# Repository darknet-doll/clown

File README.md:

# clown

A bubble-shooting clown costume. Make a gun shape with either hand, squeeze your
remaining fingers into your palm, and a comet of light runs from your upper arm
down to your fingertips — arriving exactly as a stream of bubbles starts firing out of
your fingers.

Two arms, two identical rigs — **one trigger per hand, each firing its own arm.**
LED strips hidden under gloves and sleeves, so the light reads as a glow coming
from inside the costume rather than a strip taped to your arm.

Each arm comes apart into four modules that unplug from each other, so you can get
out of the costume alone without turning into a pretzel.

**Start here:** [Clown-Build-Manual.pdf](Clown-Build-Manual.pdf) — the printable
manual. Page 1 is every part, numbered, with a plain-English note under each one;
every page after that is assembly steps referring back to those numbers.

Markdown equivalents, if you'd rather read them here:
[PARTS.md](PARTS.md) (parts and what they do) and
[BUILD.md](BUILD.md) (step-by-step assembly).

**Circuit:** [SCHEMATIC.md](SCHEMATIC.md) — two generated sheets, one for the
electronics and one for the harness. That's the drawing to review, and the one to
check your wiring against.

**Costume direction:** [DESIGN.md](DESIGN.md) — the concept board, and the three
places where it changes the build.

---

## Sequence

1. **Squeeze.** Microswitch in the palm closes.
2. **Motor kicks.** Blower gets a brief over-drive pulse to break static friction,
   then settles to its run speed.
3. **Comet launches** from pixel 0 at the pod, high on the upper arm, and travels
   toward the fingertips.
4. **~250 ms later** the comet lands at the fingertips and the blower has reached
   full speed — bubbles start. The light travel *is* the spin-up delay, so it
   reads as causal instead of as lag.
5. **Hold** to keep streaming; comets keep launching on a loop. The blower
   pulses at 5 Hz (100 ms on, 100 ms off, each burst kickstarted) rather than
   running steady — the bursts of speed form the bubbles better.
6. **Release.** Motor cuts, fingertips flare white and fade out.

---

## Why two independent arms

Each arm is a self-contained module: its own controller, battery, strip, blower,
and trigger. Nothing crosses the torso.

- No wire harness over the shoulders or back — nothing to snag, nothing to
  unplug when you take the costume off one sleeve at a time.
- **Each hand has its own trigger**, wired only to its own arm. There is no
  cross-arm wiring anywhere in v1.
- If one arm dies mid-event, the other keeps working.
- **The firmware is byte-identical on both.** As long as pixel 0 is at the pod
  on each arm, there's no handedness in the code — flash the same binary twice.

The tradeoff is buying two of everything, including two bubble maker kits and two
triggers. That's unavoidable regardless: you need one blower per hand.

*Later option:* the XIAO ESP32-C3 has ESP-NOW, so either trigger could **also** fire
the other arm for a two-handed blast. That's **additive** — each hand keeps its own
trigger and its own arm. It is a second way to fire, not a replacement for the
second trigger. Not in v1 — get one arm working end to end first.

---

## Modules and connectors

Nothing is soldered end to end across a joint. Each arm is four modules:

| Module | Holds | Unplugs at |
|---|---|---|
| **Pod** — upper arm | brain, boost, level shifter, MOSFET, fuse, disconnect, cell cradle, upper-arm strip 6 px | `SW1` + battery plug + straps |
| **Sleeve** — forearm | forearm strip, 15 px | elbow: SM 4-pin + SM 3-pin |
| **Glove** — hand | hand strip 6 px, this hand's trigger | wrist: SM 3-pin + SM 4-pin |
| **Bubbler** | bottle, cap, hose, blower head | hand: SM 2-pin + its strap |

### The connectors

| Boundary | Carries | Connector |
|---|---|---|
| Cell ↔ pod, cell ↔ charger | 2 | **JST-PH 2.0, 2-pin** *(factory, on the cell)* |
| Pod → upper-arm strip | strip 3 | **JST-SM 3-pin** |
| Strip across the elbow | strip 3 | **JST-SM 3-pin** |
| Pod → sleeve, at the elbow | motor 2 + trigger 2 | **JST-SM 4-pin** |
| Strip across the wrist | strip 3 | **JST-SM 3-pin** |
| Sleeve → glove, at the wrist | motor 2 + trigger 2 | **JST-SM 4-pin** |
| Motor ↔ bubbler, at the hand | motor 2 | **JST-SM 2-pin** |
| Microswitch pigtail | switch 2 | **JST-ZH 1.5 mm, 2-pin** |

The trigger and the motor both have to reach the pod from the hand, so they cross
*both* joints on one shared 4-pin lead — identical pinout at the elbow and the
wrist, the sleeve passes it straight through — while the strip crosses each joint
on its own 3-pin.

### Two rules that keep it safe

**No two connectors on one arm share both family and pin count** — with two
deliberate exceptions, both safe by construction. PH-2 · ZH-2 · SM-2 · SM-3 (×3) ·
SM-4 (×2): the SM-3s all carry the same strip nets in the same pin order, and the
SM-4s the same motor + trigger nets, so a cross-mate skips a segment instead of
breaking anything. The three 2-pin plugs are three different pitches — 2.0, 1.5
and 2.5 mm — so none will mate with the others.

- **The trigger pigtail is ZH, not PH,** because every cell ships on a PH2.0 lead.
  One wrong plug would put 3.7 V onto GPIO3.
- **The kit's motor lead gets reworked off PH2.0 to SM-2,** because as shipped the
  cell mates straight to the motor, bypassing the MOSFET entirely.
- The two SM-3 strip plugs — at the pod and at the elbow — are identical to each
  other, which is safe *by construction*: same strip nets, same pin order.
  Cross-mating the pod plug onto the forearm input just skips the upper-arm
  segment; nothing is damaged.

**Battery out before you mate or unmate anything.** Feeding data into an unpowered
WS2812 pushes current through its input protection diodes — the classic way to kill
pixel 0.

Full detail in [PARTS.md](PARTS.md) and [BUILD.md](BUILD.md) step 13.

---

## Power

Each arm runs off **one swappable protected 18650**, on a split rail:

```
18650 ─> SW1 ─> 2A fuse ─┬─> MOSFET ──> blower motor          (3.7V native)
                         └─> 5V boost ─┬─> LED strip + shifter (~0.3A)
                                       └─> CR2 ─> XIAO 5V pad
```

**`SW1` is a master disconnect** in the cell positive — one motion, through the
costume, kills the arm without opening the pod. The cell still comes out for
storage and charging; the switch is what makes the pod safe to open and the arm
safe to unplug in a hurry.

**`CR2` is an isolation Schottky.** The XIAO's 5V pad is tied straight to its USB-C
VBUS, so without it, plugging in to reflash with the cell connected puts the boost
output on the host port. The strip and the level shifter stay on the boost
directly at a full 5 V; only the MCU sits behind the diode.

The blower is fed straight from the cell at its native voltage — which is exactly
how Bambu designed the kit. Only the strip and the brain need boosting to 5V, and
that's a light enough load (~0.3 A) that a small inexpensive boost module is
genuinely adequate.

This is simpler than running everything from a single 5 V bus, not harder. On a
5 V rail the motor would need its PWM duty capped to ~72% to fake 3.7 V; fed
direct, it just runs, and PWM becomes purely a bubble-rate control.

Each bubble kit ships with a protected 18650 **already on a PH2.0 pigtail** and a
USB charger that mates to the same plug. Fit the matching half at the pod and a
flat cell goes pod → charger with no adapter.

That pigtail is also why the pod has **no battery sled** — the cell already carries
its own connector, so the pod only needs a printed **cradle** that holds it still
and a lid that opens without a tool. Retention and conduction stay separate jobs.

**Two cells exist, one per arm, and no spares were bought.** A flat cell ends that
arm for the night; recharging between sets is the extension plan.

The kit does **not** include a bottle — the cap fits a 24T/30T neck and you supply
the rest. That's useful: bottle size is your main lever on arm weight.

### Budget per arm

| Load | Draw |
|---|---|
| Comet at default brightness, ~8 px lit | ~0.3 A at 5V |
| Blower at run duty | ~0.5–1.0 A at 3.7V |
| **Realistic peak from the cell** | **~1.3 A** |

A 2600 mAh cell comfortably outlasts a bottle of bubble solution at any realistic
duty cycle. Swappable cells are for convenience, not because runtime is tight —
**you'll be refilling solution long before the battery matters.**

The firmware reads cell voltage through a divider and does two things with it:

- **3.4 V → warning.** The elbow pixel pulses red, slowly, once per beat. There's a
  150 mV band before it clears again, so it doesn't strobe on and off every time
  the motor loads the cell.
- **3.0 V sustained → shutoff.** The motor cuts, the trigger stops working, and
  the elbow pixel double-blinks. It latches until a charged cell turns up.

The cell's own protection board is the backstop, not the plan — repeatedly hauling
an 18650 down to its protection cutoff is what kills it. Both thresholds are
tunable at the top of the sketch.

---

## Strip layout

**Split the strip at the elbow and the wrist.** A continuous strip across a
flexing joint will crack its traces within a few hours of wear.

```
  pod              elbow                         wrist                  fingertips
   |-- upper, 6 px --|  gap  |------ forearm, 15 px ------|   gap   |-- hand, 6 px --|
   px 0          px 5        px 6                     px 20        px 21         px 26
                  ~12 cm umbilical + SM 3-pin    ~8 cm umbilical + SM 3-pin plug
```

- Upper-arm segment: ~10 cm, 6 pixels, pixel 0 at the pod, running down the upper
  arm to just above the elbow. Plugs into the pod on a **JST-SM 3-pin**.
- Elbow umbilical: ~12 cm spanning the joint, three conductors — the strip's 5V,
  GND and data — through a **JST-SM 3-pin** mated a few cm above the elbow. Service
  loop across the joint, same reasoning as the wrist.
- Forearm segment: ~21 cm, 15 pixels, just below the elbow to the wrist, under a
  sleeve.
- Wrist umbilical: ~8 cm spanning the joint, three conductors — the strip's 5V,
  GND and data — through a **JST-SM 3-pin** plug mated 3–4 cm above the wrist
  crease, where the skin barely moves. This hand's trigger and the motor cross
  beside it on their own **JST-SM 4-pin**, same pinout as the elbow's. Service
  loop on the glove side so it isn't under tension at full extension.
- Hand segment: ~10 cm, 6 pixels, across the back of the hand to the knuckles,
  under the glove.

Data chains straight through, so it's one logical 27-pixel strip in code.

The firmware knows about both physical gaps and treats them as *virtual* distance
— `ELBOW_GAP_PX` ~7 at the elbow, `GAP_PX` ~5 at the wrist — so the comet's
apparent speed stays constant as it crosses each joint instead of appearing to jump.

**Keep the umbilicals short.** Every centimetre between the last pixel on one side
of a joint and the first pixel on the other is dark arm the comet has to cross. At
the wrist ~8 cm is fine and 15 cm reads as a gap; the elbow needs more slack, but
keep it near ~12 cm.

Measure your own arm and adjust `UPPER_PX` / `FOREARM_PX` / `HAND_PX` /
`ELBOW_GAP_PX` / `GAP_PX` to match. Each gap constant is the measured
pixel-to-pixel distance across that finished umbilical — connector body included,
which is most of it — divided by 1.67 cm.

### Under the glove

Hiding the strip under fabric is a genuine upgrade, not a compromise — the fabric
diffuses the pixels into one smooth continuous streak instead of visible dots.

But it only works if the fabric cooperates:

- **Thin, pale, stretchy** fabric glows beautifully.
- **Thick or dark** fabric, especially leather, swallows almost all of it.

Test a powered strip section under your actual glove in a dark room *before*
committing to it. No firmware setting rescues a glove that eats the light.

`MAX_BRIGHTNESS` is set high (180) to punch through fabric. Route the strip over
the **back** of the hand, never the palm, and sew a fabric channel rather than
gluing the strip down taut — the channel lets it slide as your hand flexes.

Full detail in [BUILD.md](BUILD.md) step 10.

---

## Wiring

Per arm, XIAO ESP32-C3:

Full drawing: [SCHEMATIC.md](SCHEMATIC.md).

| Signal | XIAO pin | Silkscreen | To |
|---|---|---|---|
| LED data | `U3 GPIO10` | silk `D10` | 74AHCT125 input, then 330–470 Ω, then `J2` (SM-3) pin 3 |
| Trigger | `U3 GPIO3` | silk `D1` | `J3` (SM-4) pin 3 (internal pull-up, active low) |
| Motor PWM | `U3 GPIO4` | silk `D2` | MOSFET module gate input |
| Battery sense | `U3 GPIO2` | silk `D0` | Midpoint of a 100 kΩ / 100 kΩ divider across the cell |
| 5V | `U3 5V` | silk `5V` | Boost output **through `CR2`** (cathode to the XIAO) |
| GND | `U3 GND` | silk `GND` | Common ground for everything |

**Pins are named by GPIO number, parts by designator, and the two never collide.**
The diodes are `CR1` and `CR2` precisely because the XIAO's silkscreen already owns
`D0`–`D10`; the silkscreen column above is the only place those D-numbers appear.
The rule, and why it matters, is in [SCHEMATIC.md](SCHEMATIC.md#naming-rules).

Everything the pod sends down the arm leaves through two plugs:

| Plug | Pins |
|---|---|
| **`J2`, SM 3-pin** — to the upper-arm strip | 1 strip 5V · 2 strip GND · 3 strip data |
| **`J3`, SM 4-pin** — the elbow lead | 1 motor + (battery, after fuse) · 2 motor − (MOSFET output) · 3 trigger · 4 trigger return (GND) |

`J3`'s pre-crimped pigtail colors: 1 blue · 2 red · 3 green · 4 black. Red is
motor **−**, so go by pin number, not color.

The strip leaves on `J2` and goes straight into pixel 0. `J3` is a 4-conductor lead
down the upper arm to the elbow, where its SM-4 plug mates the sleeve. The strip
crosses the elbow separately, on its own SM-3 umbilical (`J6`).

Avoid `GPIO8` / `GPIO9` (silk `D8` / `D9`) — they're boot strapping pins.

Notes:

- `SW1`, a 3 A-rated DC disconnect, goes in the battery positive first, then the
  2 A polyfuse, then everything else.
- `CR2`, a 1N5819, goes between the boost output and the XIAO's 5V pad only — the
  strip and the shifter stay on the boost directly.
- A 10 kΩ gate-to-source pulldown holds the blower off while the XIAO boots. If
  your MOSFET module already has one, meter it and skip; most don't.
- The 1000 µF cap goes across the strip's 5V/GND, close to the strip connector on the pod.
- A 0.1 µF ceramic goes across the 74AHCT125's `Vcc` and `GND` pins, legs short,
  right at the chip. Different job from the 1000 µF — fit both.
- The 330–470 Ω resistor goes in series on the data line, at the connector end.
- The 1N5819 goes across the motor terminals, cathode to +, at the blower end.
- The motor is deliberately not bundled with the strip data. At the elbow it shares
  the SM-4 with the trigger, and the data crosses on its own SM-3; at the wrist the
  motor has its own SM-2. Twist the motor pair.
- Common ground is mandatory — the level shifter, strip, MOSFET, boost, and MCU
  all share it.

---

## Firmware

`firmware/clown_arm/clown_arm.ino` — Arduino sketch, FastLED, ESP32 Arduino core 3.x.

Flash the same sketch to both arms, unchanged.

Tunables live in one block at the top:

| Constant | Default | What it does |
|---|---|---|
| `UPPER_PX` / `FOREARM_PX` / `HAND_PX` | 6 / 15 / 6 | Physical layout |
| `ELBOW_GAP_PX` / `GAP_PX` | 7 / 5 | Virtual distance across the elbow and wrist umbilicals |
| `COMET_TRAVEL_MS` | 250 | Pod to fingertip, must match blower spin-up |
| `COMET_REPEAT_MS` | 320 | Gap between comets while held |
| `MAX_BRIGHTNESS` | 180 | Global cap — raised to punch through glove fabric |
| `IDLE_BRIGHTNESS` | 20 | Resting glow; 0 for fully dark |
| `MOTOR_RUN_DUTY` | 230 | Bubble rate |
| `MOTOR_KICK_DUTY` / `MOTOR_KICK_MS` | 255 / 80 | Kickstart pulse |
| `MOTOR_PULSE_PERIOD_MS` / `MOTOR_PULSE_ON_MS` | 200 / 100 | 5 Hz, 50% bursts while held; ON = PERIOD for steady |
| `THEME_HUE` | 192 | Idle glow and release flare color |
| `RAINBOW_DRIFT_MS` | 8 | Comet is a rainbow; ms per hue step of drift (lower = faster) |
| `VBAT_WARN_MV` / `VBAT_WARN_CLEAR_MV` | 3400 / 3550 | Low-cell warning, with hysteresis |
| `VBAT_CUTOFF_MV` | 3000 | Sustained → shut the arm down |

Tune `COMET_TRAVEL_MS` last, on the assembled arm: film it in slow motion and
adjust until the first bubble leaves your fingers on the same frame the comet
lands. See [BUILD.md](BUILD.md) step 9.

---

## Field notes

- **Soap gets everywhere, and "above the spray" is a lie at a rave.** Your arms go
  up; the pod is then under the runoff, not above it. Sealed, drained, downward-
  facing openings, drip loops on every wire — [BUILD.md](BUILD.md) step 11.
- **`SW1` off, then cell out.** In that order, every time you stop.
- **Test the trigger in the gun pose, not on the bench.** The lever needs to sit
  under your middle and ring finger pads so the squeeze lands every time without
  aiming.
- **Cell out before you mate or unmate any connector.** Every time. It is the one
  habit that protects pixel 0.
- **Carry spares:** pre-made wrist and elbow umbilicals, and one SM pigtail pair of
  each size. Those swap without a soldering iron.
- **Know the two you can't fix:** a flat cell and a dead trigger. One of each per
  arm, both in use, no spares bought — see [BUILD.md](BUILD.md)'s field kit.
- **Any cell that ever travels loose gets a plastic case**, never a bag with keys
  or coins. The whole can of an 18650 is its negative terminal and the wrap is all
  that covers it.
- **Check every latch before you walk out.** A half-seated SM plug looks mated and
  works until you move.
- **Keep the USB-C port accessible** in the printed pod. You will reflash this
  more often than you expect.

---

## Status

- [x] Design, power plan, wiring
- [x] Parts list with explanations — [PARTS.md](PARTS.md)
- [x] Build manual — [BUILD.md](BUILD.md)
- [x] Printable PDF manual — [Clown-Build-Manual.pdf](Clown-Build-Manual.pdf)
- [x] Firmware v1, incl. low-battery warning with hysteresis and a 3.0 V shutoff
- [x] Schematic and harness drawing — [SCHEMATIC.md](SCHEMATIC.md)
- [x] Concept direction — [DESIGN.md](DESIGN.md)
- [x] Connector architecture — four modules per arm, no soldered joints across a joint
- [ ] **Pull the kit's technical drawings from the Bambu site** — needed for the
      bubbler mount and the blower sleeve. Interim: the pocket a third-party gun
      cut for the same head is measured in
      [3d-prints/bubble-housing](3d-prints/bubble-housing/bubble-housing.md)
- [ ] **Find the IR / thermal camera** — wanted for bench test, [BUILD.md](BUILD.md) step 6
- [ ] **Hose test** — does a 150 mm feed hose still lift solution? Decides Mount C
      vs Mount A ([BUILD.md](BUILD.md) step 7)
- [ ] Pick a multimeter — spec and three suggestions in [PARTS.md](PARTS.md)
- [ ] Decide leaded vs lead-free solder (tradeoff in [PARTS.md](PARTS.md))
- [ ] Source a **logic-level** MOSFET — *not* an IRF520 module, see [PARTS.md](PARTS.md)
- [x] Kits, passives, protoboards and triggers on hand — see
      [PARTS.md](PARTS.md), *What's already on hand*
- [ ] Remaining parts ordered — the `buy` rows in [PARTS.md](PARTS.md); **stock,
      price and delivery are unverified**, confirm in cart
- [ ] Costume layer decided — glove, sleeve, diffuser, ribbon. Buy one, test it
      lit, then buy the rest
- [ ] Bottles sourced — 24T/30T neck, not included in the kit
- [ ] Lace diffusion test (see DESIGN.md — lace reveals, it doesn't diffuse)
- [ ] Decide where the controller pod hides
- [ ] One arm assembled and timed
- [ ] Second arm
- [ ] Both-arms checkout and doffing drill ([BUILD.md](BUILD.md) step 13)
- [ ] **Engineering review of [SCHEMATIC.md](SCHEMATIC.md)** — checklist at the
      bottom of that file
- [ ] Printed enclosures (trigger plate, cell cradle, controller pod, bubbler
      mount) — sealed to [BUILD.md](BUILD.md) step 11, not just printed
- [ ] **Soak test** — powered arm, overhead, sprayed for a minute, then opened and
      inspected ([BUILD.md](BUILD.md) step 11)
- [ ] Source the disconnect switches — **check the DC rating**, not the AC one
- [ ] Optional: ESP-NOW sync between arms

---

## Regenerating the PDF

The manual is generated, not hand-edited. Edit
[docs/manual/build_manual.py](docs/manual/build_manual.py) and run:

```
pip3 install reportlab
python3 docs/manual/build_manual.py
```

Part numbers live in the `PARTS` list at the top of that script; the assembly
steps reference them through `ref(n)`, so renumbering a part updates every
cross-reference automatically.

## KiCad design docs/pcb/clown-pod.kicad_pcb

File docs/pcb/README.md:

# Pod PCB

The pod circuit from the [perfboard layout](../layout/README.md) as a real
two-layer board. Same parts, same nets and same designators as
[SCHEMATIC.md](../../SCHEMATIC.md). Everything is through-hole and hand-soldered.

| File | What it is |
|---|---|
| [fab/clown-pod-gerbers.zip](fab/clown-pod-gerbers.zip) | **The upload for PCBWay.** Gerbers for copper, mask, silk and outline, plus Excellon drill files |
| [clown-pod.kicad_pcb](clown-pod.kicad_pcb) | The board, opens in KiCad 9 |
| [pod_pcb.py](pod_pcb.py) | The source: outline, placement, netlist, hand-routed power, silkscreen |
| [build.sh](build.sh) | Rebuilds everything: place, autoroute, ground pour, DRC, export |
| [pod-pcb-build.html](pod-pcb-build.html) | **Soldering walkthrough.** One part per step, in build order, with a meter check after each group. Published copy: [Pod PCB Build](https://claude.ai/artifact/EFubpZgKECGwYLr3vCSfxH). Edit both together |

## Parts the footprints were sized to

Measured, not assumed:

- **C1, the 1000 µF cap: 10 mm across**, 5 mm lead pitch. It clears U2, R3 and
  Q1 by about 0.5 mm. A fatter can won't fit
- **F1, the GBX polyfuse: a 15 mm disc on 5 mm-pitch legs**, standing upright.
  Its kinked legs hold it 3 mm off the board. It sits in the bottom row between
  U1's pads and SW1, and its outline is the disc seen from above

## Ordering on PCBWay

Upload `fab/clown-pod-gerbers.zip` as a standard PCB. The size and layer count
come from the files. Set these on the form; everything else stays at its
default:

| Setting | Value |
|---|---|
| Size / quantity | 70 × 30 mm, single pieces, 5 boards (the minimum: one per arm, three spares) |
| Layers | 2 |
| Material / thickness | FR-4, 1.6 mm |
| Copper | 1 oz |
| Min track / spacing | 0.3 mm / 0.4 mm. Well inside the standard 6/6 mil |
| Min hole | 0.4 mm (vias). The smallest part hole is 0.8 mm |
| Via process | Tenting vias |
| Surface finish | **HASL lead-free.** Not the default: the form starts on leaded HASL |
| Solder mask / silkscreen | Any colour. Green with white silk is the cheapest and fastest |
| Remove product No. | **Yes.** Otherwise PCBWay prints its order number on the silkscreen |

Order the bare board only. No assembly, no stencil: the parts are already in
hand (see [PARTS.md](../../PARTS.md)).

## The board

- **70 × 30 mm, an M2 hole 2.5 mm in from each corner.** That's the size of the
  3 × 7 cm perfboard it replaces. No copper, pour included, comes within 2.4 mm
  of a hole centre, so M2 screw heads, nuts and standoffs are safe. M3 hardware is not. Check the
  holes against the pod cradle when that gets designed
- **U3 (XIAO) sits on two 7-pin headers, USB-C off the left edge.** The module
  overhangs the board by 0.4 mm, so its USB-C socket stands about 1.5 mm proud
  and a cable reaches it through the pod wall. Pin 1 (`U3 GPIO2`) is the square
  pad, and pin 14 (`U3 5V`) is directly across from it. Nothing goes under the
  module
- **U2 is a plain DIP-14 footprint.** Solder the chip or fit a socket. A socket
  isn't in PARTS.md
- **Off-board parts land on wire pads.** These are `U1` (the MT3608 module), `SW1`,
  `J1` (the cell's PH2.0 lead), `J2` (strip SM-3) and `J3` (elbow SM-4). Pad 1 of
  each is square. Pad names are under the bottom-row pads; J2 and J3 are labelled
  with pin and job. U1's pads run `OUT− OUT+ IN− IN+` left to right
- **Check a few solder-side spots under a magnifier after soldering.** These
  pass DRC with margin, but a solder bridge at any of them is costly:
  - U2 pins 1–4 next to the `GATE_3V3` track
  - U2 pins 9 and 12 next to the +5 V trunk
  - the SW1 pads next to the VBATT track
- **The power stage is at the right-hand end**, beside J3: cell, switch, fuse
  and Q1. The motor current loop stays short and never crosses the logic
- **Power is routed by hand and locked.** The router does only the signals:
  - The cell, switch, fuse and motor path is 1.5 mm wide. It carries about 2 A
    firing and about 3 A in the 80 ms kick
  - The +5 V trunk runs U1 → C1 → J2 at 1.0 mm, so strip current never flows
    through U2's pins
  - U2 and the XIAO branch off the trunk
- **Ground is poured, not routed.** Both layers carry a ground pour, stitched
  with 55 vias. Q1's source ties solid to the pour, with no thermal spokes
- **Polarity is on the silkscreen.** `CR2` has its band and `K` toward the XIAO.
  `C1` has its `+` beside the square pad, and `Q1` is marked `G D S` with its
  tab toward C1. The board's height budget: Q1 stands about 20 mm, C1 17–22 mm
  and the XIAO about 8 mm

Two parts here go beyond the perfboard. Both are on the schematic:

- **R6, 100 k from `U2 2A` to GND.** Until `setup()` drives `U3 GPIO4`, U2's
  motor input floats, and U2 drives the MOSFET gate from it. R5 can't overpower
  a driven output, so without R6 the blower can twitch at power-up
- **C3, 0.1 µF across R2.** It filters the battery-sense divider for the ADC.
  It sits between U3 and U2, because there's no room at the ADC pin. For a slow
  battery reading, where it sits on the net doesn't matter

Four short net stretches get names here that the schematic draws but doesn't
name. `VBATT_RAW` is `J1-1` to `SW1`, and `VBATT_SW` is `SW1` to `F1`.
`GATE_Q` is `R4` to `Q1 G` and `R5`. `LED_DATA_STRIP` is `R3` to `J2-3`.

## Rebuilding

```
docs/pcb/build.sh
```

Needs Docker and Java 17+. KiCad 9 runs from the `kicad/kicad:9.0.4` image, and
Freerouting 2.1.0 is downloaded to `~/.cache/freerouting` the first time. The
script stops if DRC finds any error or unconnected pad. Silkscreen off the board
edge, over pads, or under 0.8 mm / 0.15 mm counts as an error. `build/` holds
intermediates and is ignored. Edit `pod_pcb.py`, never the `.kicad_pcb`: the
board is regenerated from scratch on every run.

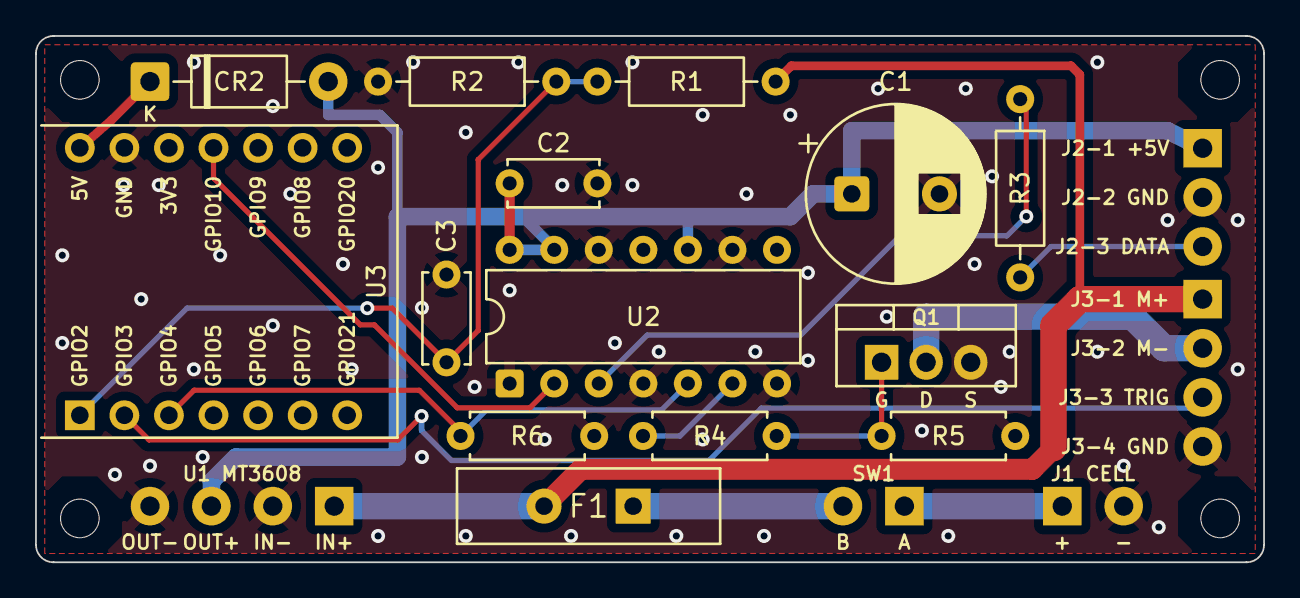
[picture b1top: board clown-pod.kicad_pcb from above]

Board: 2 copper layers, 70.0 x 30.0 mm, 23 parts (0 on the bottom side), 15 nets.

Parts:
C1: 1000uF 16V; CP_Radial_D10.0mm_P5.00mm
C2, C3: 0.1uF; C_Disc_D5.0mm_W2.5mm_P5.00mm
CR2: 1N5819; D_DO-41_SOD81_P10.16mm_Horizontal
F1: PPTC 1.85-2.5A; PPTC_Disc_D15mm_P5.08mm
H1, H2, H3, H4: MountingHole_2.2mm_M2
J1: Cell, PH2.0; WirePads_2
J2: Strip SM-3; WirePads_3
J3: Elbow SM-4; WirePads_4
Q1: RFP30N06LE; TO-220-3_Vertical
R1, R2: 100k; R_Axial_DIN0207_L6.3mm_D2.5mm_P10.16mm_Horizontal
R3: 470R; R_Axial_DIN0207_L6.3mm_D2.5mm_P10.16mm_Horizontal
R4: 100R; R_Axial_DIN0207_L6.3mm_D2.5mm_P7.62mm_Horizontal
R5: 10k; R_Axial_DIN0207_L6.3mm_D2.5mm_P7.62mm_Horizontal
R6: 100k; R_Axial_DIN0207_L6.3mm_D2.5mm_P7.62mm_Horizontal
SW1: KCD1 rocker; WirePads_2
U1: MT3608 module; WirePads_4
U2: 74AHCT125; DIP-14_W7.62mm
U3: XIAO ESP32-C3; XIAO_ESP32C3_Headers

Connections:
+5V: C1.1, C2.1, CR2.2, J2.1, U1.3, U2.10, U2.13, U2.14
+5V_MCU: CR2.1, U3.14
GATE: R4.1, U2.6
GATE_3V3: R6.1, U2.5, U3.3
GATE_Q: Q1.1, R4.2, R5.1
GND: C1.2, C2.2, C3.2, J1.2, J2.2, J3.4, Q1.3, R2.2, R5.2, R6.2, U1.2, U1.4, U2.1, U2.4, U2.7, U2.9, U2.12, U3.13
LED_DATA: R3.1, U2.3
LED_DATA_3V3: U2.2, U3.11
LED_DATA_STRIP: J2.3, R3.2
MOTOR-: J3.2, Q1.2
TRIG: J3.3, U3.2
VBATT: F1.2, J3.1, R1.1, U1.1
VBATT_RAW: J1.1, SW1.1
VBATT_SW: F1.1, SW1.2
VSENSE: C3.1, R1.2, R2.1, U3.1

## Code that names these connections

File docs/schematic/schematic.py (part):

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# The only place the XIAO's silkscreen D-numbers are allowed to appear, besides
# the silk map printed under U3 on sheet 1. Everything else says GPIOn.
PINMAP = [
    ("U3 GPIO2", "D0", "VSENSE", "ADC, battery divider midpoint"),
    ("U3 GPIO3", "D1", "TRIG", "Input, internal pull-up, switch pulls it low"),
    ("U3 GPIO4", "D2", "GATE_3V3", "Output, motor PWM into U2 2A"),
    ("U3 GPIO10", "D10", "LED_DATA_3V3", "Output, pixel data into U2 1A"),
    ("U3 5V", "5V", "+5V_MCU", "Power in, behind CR2"),
    ("U3 GND", "GND", "GND", "The one ground"),
]
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    s.block(560, 700, 220, 260, "U3", "XIAO ESP32-C3", "keep USB-C reachable")
    s.pin(560, 750, "l", "5V")
    g3 = s.pin(560, 800, "l", "GND")
    vsense_pin = s.pin(560, 850, "l", "GPIO2")
    trig_pin = s.pin(560, 900, "l", "GPIO3")
    gate_pin = s.pin(780, 790, "r", "GPIO4")
    data_pin = s.pin(780, 840, "r", "GPIO10")
    s.wire([g3, (500, 800)])
    s.gnd(500, 800)
    s.flag(vsense_pin[0] - 18, 850, "VSENSE", "l")
    s.wire([(vsense_pin[0] - 18, 850), vsense_pin])
    s.flag(trig_pin[0] - 18, 900, "TRIG", "l")
    s.wire([(trig_pin[0] - 18, 900), trig_pin])
    s.text(670, 926, "silk map: GPIO2 = D0 · GPIO3 = D1", size=9,
           anchor="middle", fill=MUTED)
    s.text(670, 942, "GPIO4 = D2 · GPIO10 = D10", size=9,
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    ug = s.pin(940, 990, "b", "GND")
    oe1 = s.pin(1010, 990, "b", "1OE")
    oe2 = s.pin(1080, 990, "b", "2OE")
    s.wire([gate_pin, a2])
    s.wire([data_pin, a1])

    # to Vcc: the rail, and the two disabled output-enables
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    s.text(232, 1300, "holds the gate down", size=10, anchor="end")
    s.text(232, 1316, "while U2 is unpowered", size=10, anchor="end")

    # R6: U2 2A floats until setup() drives GPIO4, and U2 drives GATE from it
    s.flag(60, 1180, "GATE_3V3", "r")
    s.wire([(178, 1180), (230, 1180), (230, 1186)])
    s.resistor(230, 1220, "v", "R6", "100 k")
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                     (LDATA, "LED_DATA  from R3")):
        s.text(80, y - 10, label, size=10)
        s.wire([(100, y), j2[{L5V: 0, LGND: 1, LDATA: 2}[y]][0]])
    for i, (y, label) in enumerate(((MP, "MOTOR+  VBATT after F1"),
                                    (MN, "MOTOR-  Q1 D"),
                                    (ETRIG, "TRIG  to U3 GPIO3"),
                                    (ERTN, "trigger return  GND"))):
        s.text(80, y - 10, label, size=10)
        s.wire([(100, y), j3[i][0]])
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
